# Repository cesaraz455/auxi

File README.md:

# auxi

**auxi** es un pequeño robot de fútbol para una competencia universitaria de robots, un proyecto de primer semestre. Este repositorio contiene el diseño en KiCad de su única PCB.

Toda la documentación del proyecto (decisiones de diseño, alimentación, pines, conectores, chasis, armado de la placa y puntos abiertos) está en un solo archivo: **[`CLAUDE.md`](CLAUDE.md)**.

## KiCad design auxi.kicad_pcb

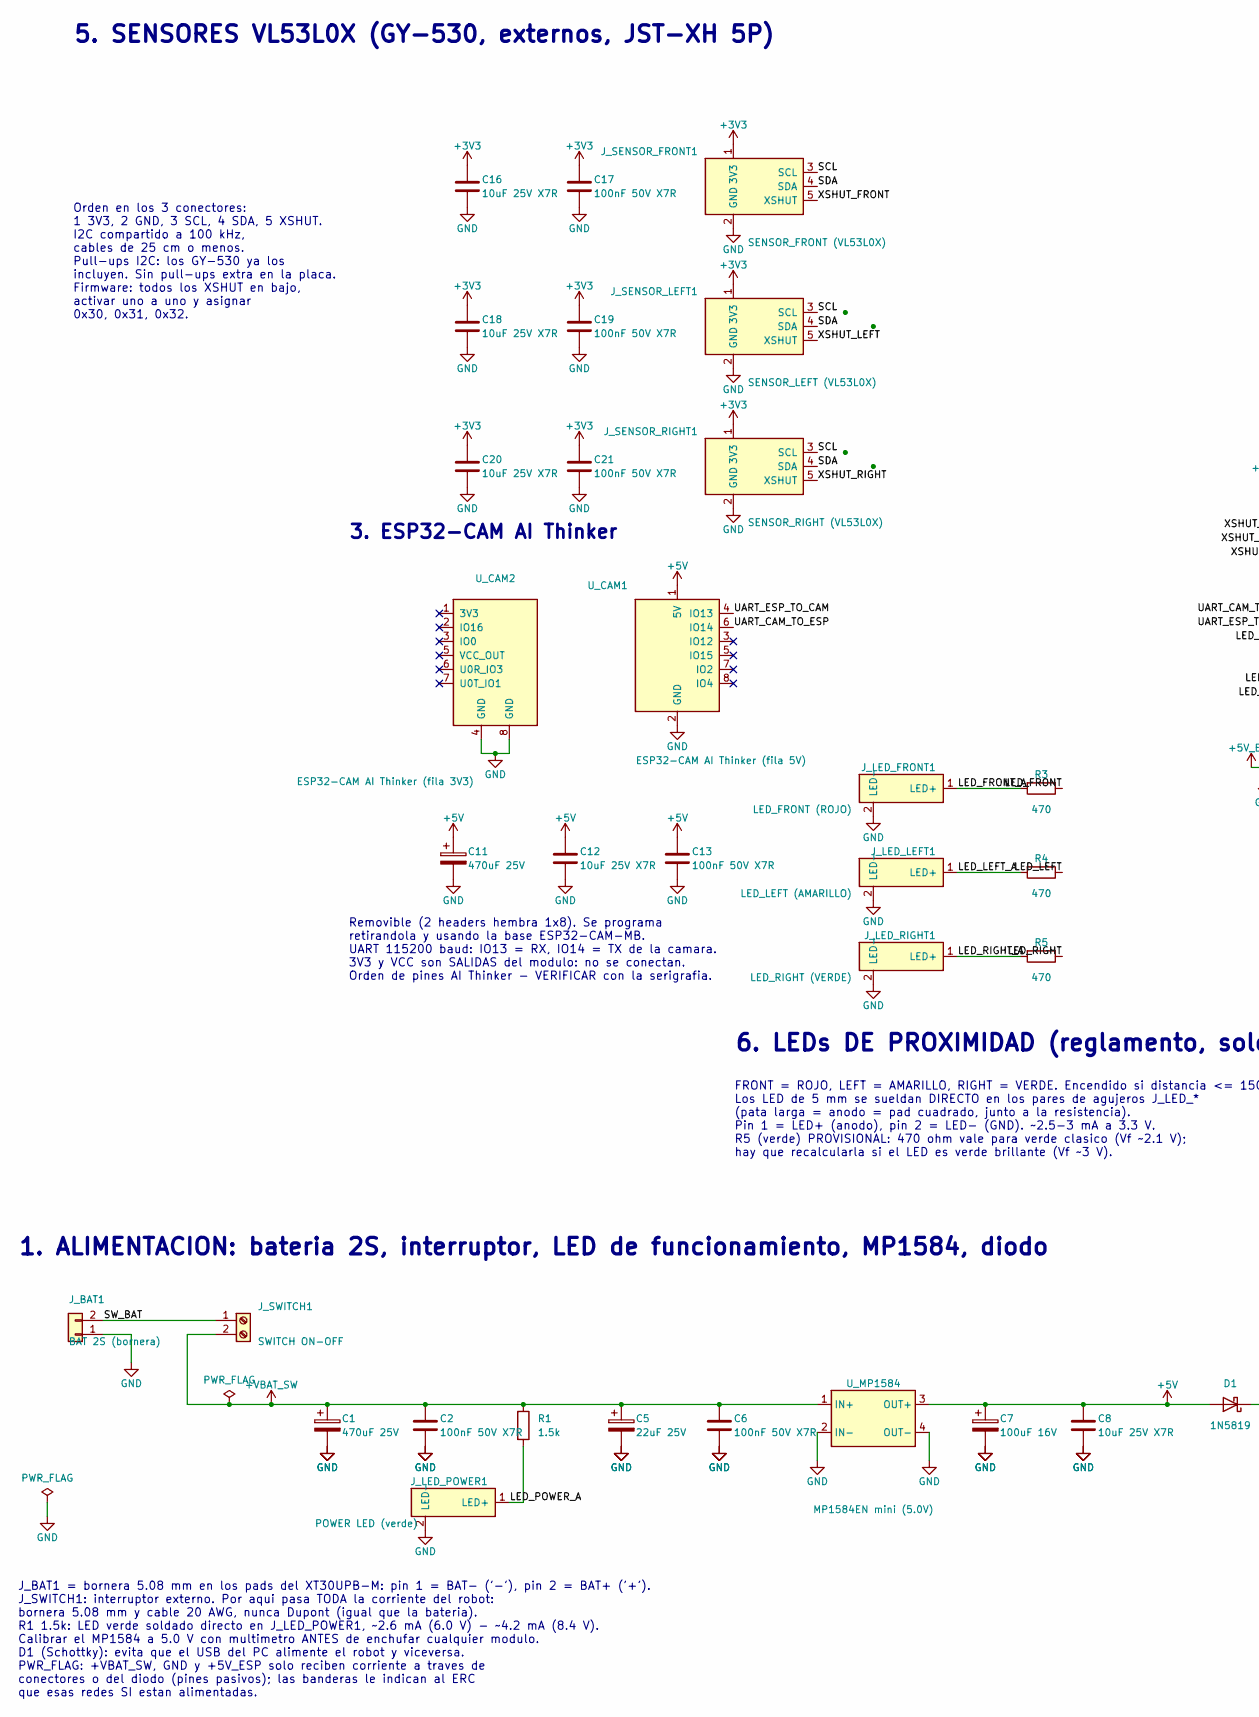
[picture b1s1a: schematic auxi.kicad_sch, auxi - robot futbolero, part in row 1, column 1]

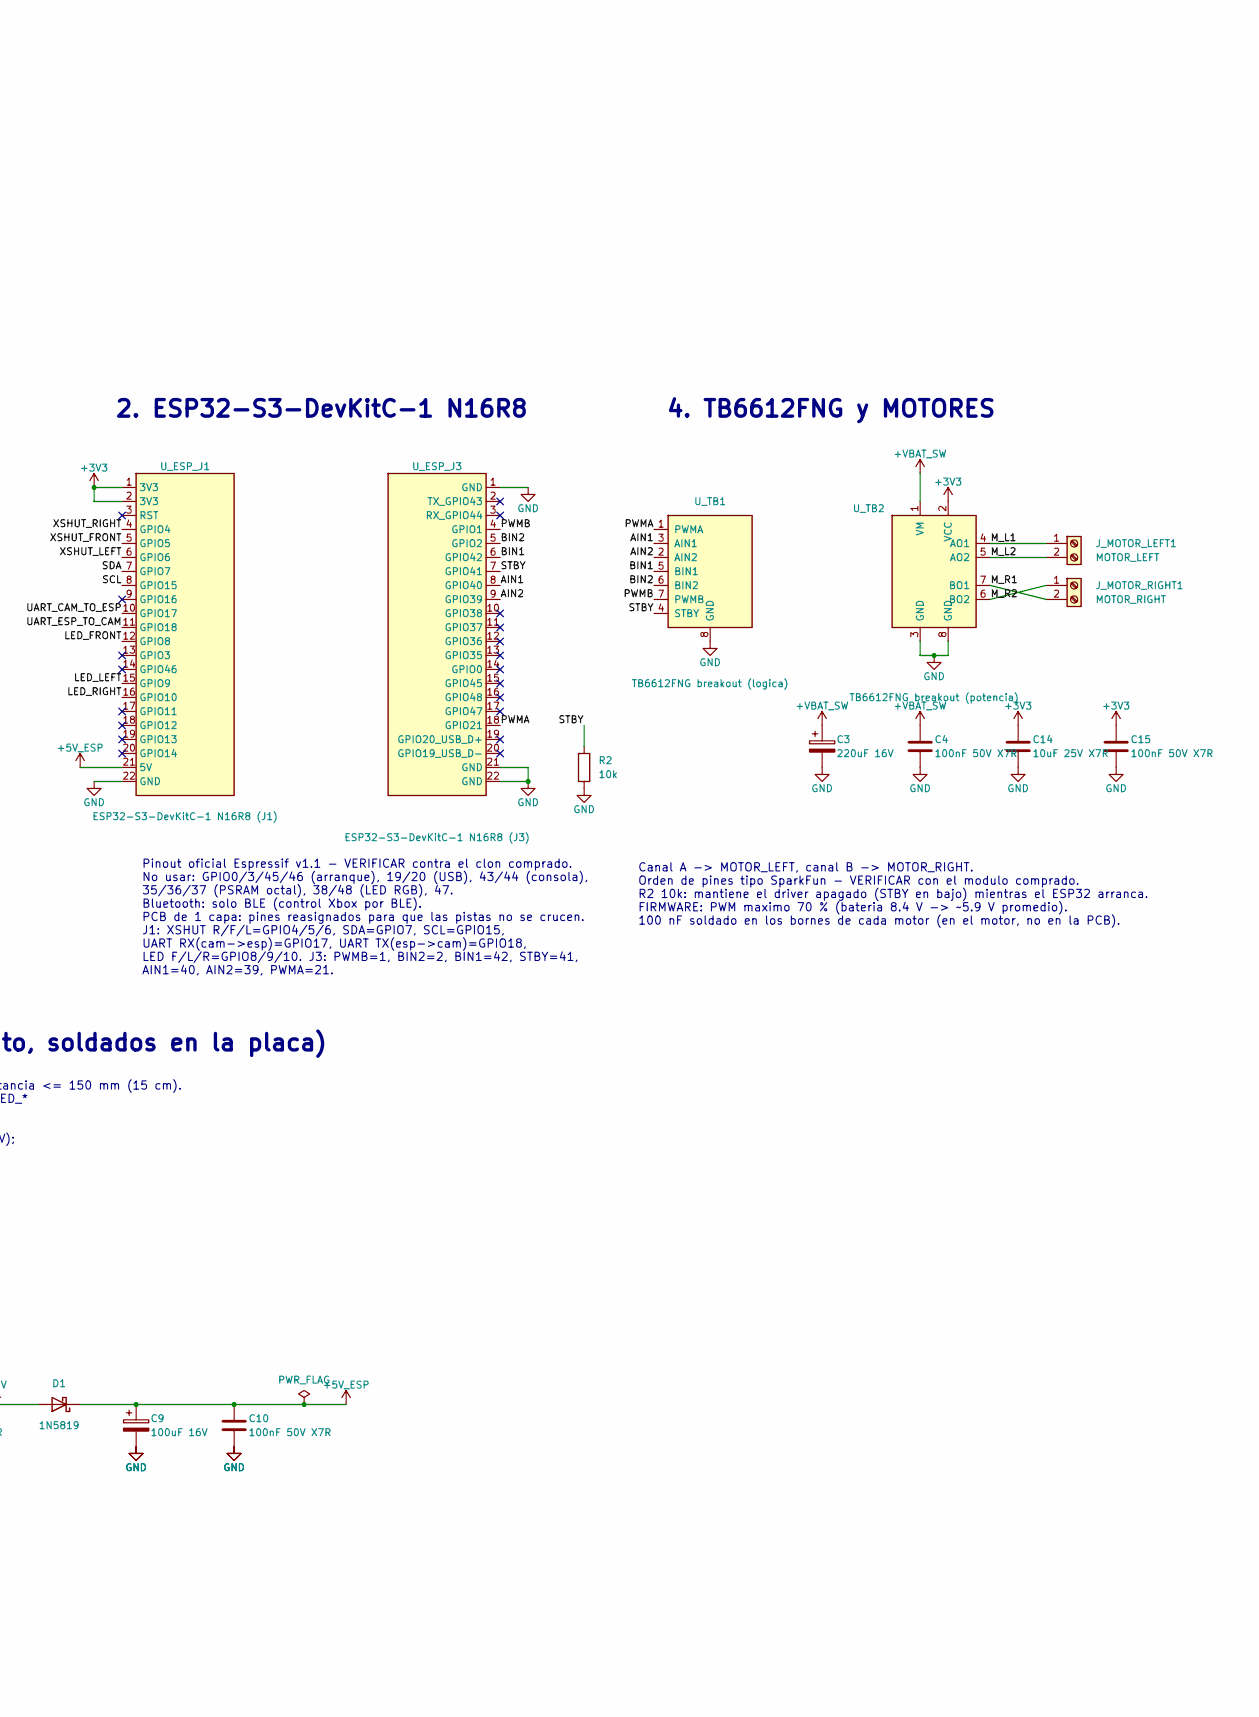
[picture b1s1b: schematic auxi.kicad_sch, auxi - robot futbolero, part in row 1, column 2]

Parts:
C1, C11: 470uF 25V; CP_Radial_D10.0mm_P5.00mm
C2, C4, C6, C10, C13, C15, C17, C19, C21: 100nF 50V X7R; C_Disc_D5.0mm_W2.5mm_P5.00mm
C3: 220uF 16V; CP_Radial_D8.0mm_P3.50mm
C5: 22uF 25V; CP_Radial_D5.0mm_P2.00mm
C7, C9: 100uF 16V; CP_Radial_D6.3mm_P2.50mm
C8, C12, C14, C16, C18, C20: 10uF 25V X7R; C_Rect_L7.0mm_W3.5mm_P5.00mm
D1: 1N5819; D_DO-41_SOD81_P10.16mm_Horizontal
J_BAT1: BAT 2S (bornera); AMASS_XT30UPB-M_1x02_P5.0mm_Vertical
J_LED_FRONT1: LED_FRONT (ROJO); PinHeader_1x02_P2.54mm_Vertical
J_LED_LEFT1: LED_LEFT (AMARILLO); PinHeader_1x02_P2.54mm_Vertical
J_LED_POWER1: POWER LED (verde); PinHeader_1x02_P2.54mm_Vertical
J_LED_RIGHT1: LED_RIGHT (VERDE); PinHeader_1x02_P2.54mm_Vertical
J_MOTOR_LEFT1: MOTOR_LEFT; TerminalBlock_Phoenix_MKDS-1,5-2-5.08_1x02_P5.08mm_Horizont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
J_MOTOR_RIGHT1: MOTOR_RIGHT; TerminalBlock_Phoenix_MKDS-1,5-2-5.08_1x02_P5.08mm_Horizont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
J_SENSOR_FRONT1: SENSOR_FRONT (VL53L0X); JST_XH_B5B-XH-A_1x05_P2.50mm_Vertical
J_SENSOR_LEFT1: SENSOR_LEFT (VL53L0X); JST_XH_B5B-XH-A_1x05_P2.50mm_Vertical
J_SENSOR_RIGHT1: SENSOR_RIGHT (VL53L0X); JST_XH_B5B-XH-A_1x05_P2.50mm_Vertical
J_SWITCH1: SWITCH ON-OFF; TerminalBlock_Phoenix_MKDS-1,5-2-5.08_1x02_P5.08mm_Horizont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
R1: 1.5k; R_Axial_DIN0207_L6.3mm_D2.5mm_P7.62mm_Horizontal
R2: 10k; R_Axial_DIN0207_L6.3mm_D2.5mm_P7.62mm_Horizontal
R3, R4, R5: 470; R_Axial_DIN0207_L6.3mm_D2.5mm_P7.62mm_Horizontal
U_CAM1: ESP32-CAM AI Thinker (fila 5V); PinSocket_1x08_P2.54mm_Vertical
U_CAM2: ESP32-CAM AI Thinker (fila 3V3); PinSocket_1x08_P2.54mm_Vertical
U_ESP_J1: ESP32-S3-DevKitC-1 N16R8 (J1); PinSocket_1x22_P2.54mm_Vertical
U_ESP_J3: ESP32-S3-DevKitC-1 N16R8 (J3); PinSocket_1x22_P2.54mm_Vertical
U_MP1584: MP1584EN mini (5.0V); MP1584_Mini_PROVISIONAL
U_TB1: TB6612FNG breakout (logica); PinSocket_1x08_P2.54mm_Vertical
U_TB2: TB6612FNG breakout (potencia); PinSocket_1x08_P2.54mm_Vertical

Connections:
+3V3: C14.1, C15.1, C16.1, C17.1, C18.1, C19.1, C20.1, C21.1, J_SENSOR_FRONT1.1 (3V3), J_SENSOR_LEFT1.1 (3V3), J_SENSOR_RIGHT1.1 (3V3), U_ESP_J1.1 (3V3), U_ESP_J1.2 (3V3), U_TB2.2 (VCC)
+5V: C7.1, C8.1, C11.1, C12.1, C13.1, D1.2 (A), U_CAM1.1 (5V), U_MP1584.3 (OUT+)
+5V_ESP: C9.1, C10.1, D1.1 (K), U_ESP_J1.21 (5V)
+VBAT_SW: C1.1, C2.1, C3.1, C4.1, C5.1, C6.1, J_SWITCH1.2, R1.1, U_MP1584.1 (IN+), U_TB2.1 (VM)
AIN1: U_ESP_J3.8 (GPIO40), U_TB1.3 (AIN1)
AIN2: U_ESP_J3.9 (GPIO39), U_TB1.2 (AIN2)
BIN1: U_ESP_J3.6 (GPIO42), U_TB1.5 (BIN1)
BIN2: U_ESP_J3.5 (GPIO2), U_TB1.6 (BIN2)
GND: C1.2, C2.2, C3.2, C4.2, C5.2, C6.2, C7.2, C8.2, C9.2, C10.2, C11.2, C12.2, C13.2, C14.2, C15.2, C16.2, C17.2, C18.2, C19.2, C20.2, C21.2, J_BAT1.1, J_LED_FRONT1.2 (LED-), J_LED_LEFT1.2 (LED-), J_LED_POWER1.2 (LED-), J_LED_RIGHT1.2 (LED-), J_SENSOR_FRONT1.2 (GND), J_SENSOR_LEFT1.2 (GND), J_SENSOR_RIGHT1.2 (GND), R2.2, U_CAM1.2 (GND), U_CAM2.4 (GND), U_CAM2.8 (GND), U_ESP_J1.22 (GND), U_ESP_J3.1 (GND), U_ESP_J3.21 (GND), U_ESP_J3.22 (GND), U_MP1584.2 (IN-), U_MP1584.4 (OUT-), U_TB1.8 (GND), U_TB2.3 (GND), U_TB2.8 (GND)
LED_FRONT: R3.1, U_ESP_J1.12 (GPIO8)
LED_FRONT_A: J_LED_FRONT1.1 (LED+), R3.2
LED_LEFT: R4.1, U_ESP_J1.15 (GPIO9)
LED_LEFT_A: J_LED_LEFT1.1 (LED+), R4.2
LED_POWER_A: J_LED_POWER1.1 (LED+), R1.2
LED_RIGHT: R5.1, U_ESP_J1.16 (GPIO10)
LED_RIGHT_A: J_LED_RIGHT1.1 (LED+), R5.2
M_L1: J_MOTOR_LEFT1.1, U_TB2.4 (AO1)
M_L2: J_MOTOR_LEFT1.2, U_TB2.5 (AO2)
M_R1: J_MOTOR_RIGHT1.2, U_TB2.7 (BO1)
M_R2: J_MOTOR_RIGHT1.1, U_TB2.6 (BO2)
PWMA: U_ESP_J3.18 (GPIO21), U_TB1.1 (PWMA)
PWMB: U_ESP_J3.4 (GPIO1), U_TB1.7 (PWMB)
SCL: J_SENSOR_FRONT1.3 (SCL), J_SENSOR_LEFT1.3 (SCL), J_SENSOR_RIGHT1.3 (SCL), U_ESP_J1.8 (GPIO15)
SDA: J_SENSOR_FRONT1.4 (SDA), J_SENSOR_LEFT1.4 (SDA), J_SENSOR_RIGHT1.4 (SDA), U_ESP_J1.7 (GPIO7)
STBY: R2.1, U_ESP_J3.7 (GPIO41), U_TB1.4 (STBY)
SW_BAT: J_BAT1.2, J_SWITCH1.1
UART_CAM_TO_ESP: U_CAM1.6 (IO14), U_ESP_J1.10 (GPIO17)
UART_ESP_TO_CAM: U_CAM1.4 (IO13), U_ESP_J1.11 (GPIO18)
XSHUT_FRONT: J_SENSOR_FRONT1.5 (XSHUT), U_ESP_J1.5 (GPIO5)
XSHUT_LEFT: J_SENSOR_LEFT1.5 (XSHUT), U_ESP_J1.6 (GPIO6)
XSHUT_RIGHT: J_SENSOR_RIGHT1.5 (XSHUT), U_ESP_J1.4 (GPIO4)

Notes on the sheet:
1. ALIMENTACION: bateria 2S, interruptor, LED de funcionamiento, MP1584, diodo
J_BAT1 = bornera 5.08 mm en los pads del XT30UPB-M: pin 1 = BAT- ('-'), pin 2 = BAT+ ('+'). J_SWITCH1: interruptor externo. Por aqui pasa TODA la corriente del robot: bornera 5.08 mm y cable 20 AWG, nunca Dupont (igual que la bateria). R1 1.5k: LED verde soldado directo en J_LED_POWER1, ~2.6 mA (6.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
2. ESP32-S3-DevKitC-1 N16R8
Pinout oficial Espressif v1.1 - VERIFICAR contra el clon comprado. No usar: GPIO0/3/45/46 (arranque), 19/20 (USB), 43/44 (consola), 35/36/37 (PSRAM octal), 38/48 (LED RGB), 47. Bluetooth: solo BLE (control Xbox por BLE). PCB de 1 capa: pines reasignados para que las pistas no se crucen. J1: XSHUT R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
3. ESP32-CAM AI Thinker
Removible (2 headers hembra 1x8). Se programa retirandola y usando la base ESP32-CAM-MB. UART 115200 baud: IO13 = RX, IO14 = TX de la camara. 3V3 y VCC son SALIDAS del modulo: no se conectan. Orden de pines AI Thinker - VERIFICAR con la serigrafia.
4. TB6612FNG y MOTORES
Canal A -> MOTOR_LEFT, canal B -> MOTOR_RIGHT. Orden de pines tipo SparkFun - VERIFICAR con el modulo comprado. R2 10k: mantiene el driver apagado (STBY en bajo) mientras el ESP32 arranca. FIRMWARE: PWM maximo 70 % (bateria 8.4 V -> ~5.9 V promedio). 100 nF soldado en los bornes de cada motor (en e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
5. SENSORES VL53L0X (GY-530, externos, JST-XH 5P)
Orden en los 3 conectores: 1 3V3, 2 GND, 3 SCL, 4 SDA, 5 XSHUT. I2C compartido a 100 kHz, cables de 25 cm o menos. Pull-ups I2C: los GY-530 ya los incluyen. Sin pull-ups extra en la placa. Firmware: todos los XSHUT en bajo, activar uno a uno y asignar 0x30, 0x31, 0x32.
6. LEDs DE PROXIMIDAD (reglamento, soldados en la placa)
FRONT = ROJO, LEFT = AMARILLO, RIGHT = VERDE. Encendido si distancia <= 150 mm (15 cm). Los LED de 5 mm se sueldan DIRECTO en los pares de agujeros J_LED_* (pata larga = anodo = pad cuadrado, junto a la resistencia). Pin 1 = LED+ (anodo), pin 2 = LED- (GND). ~2.5-3 mA a 3.3 V. R5 (verde) PROVISIONA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

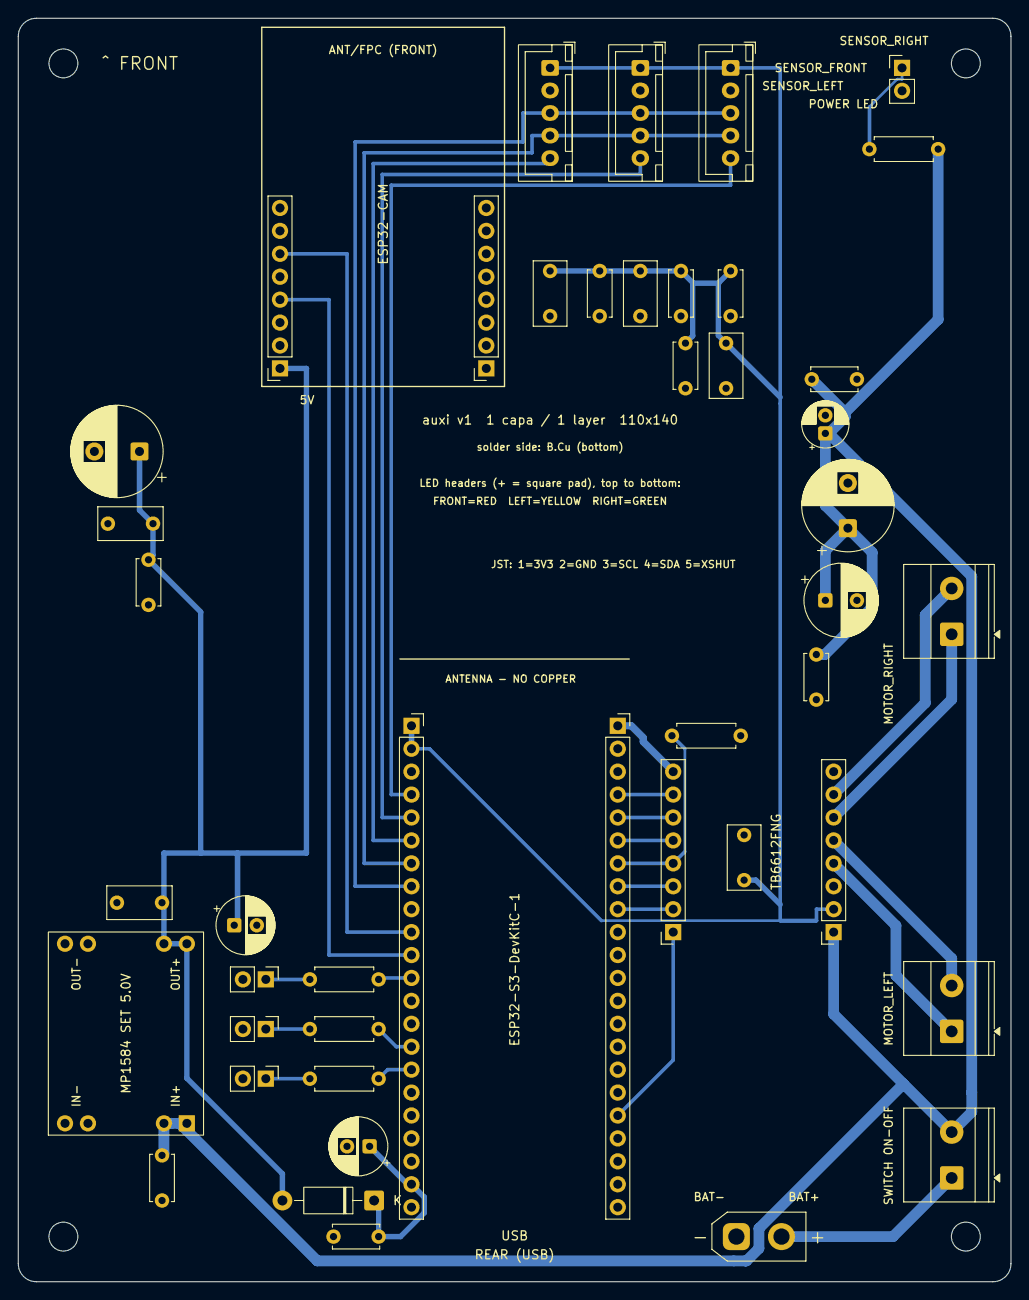
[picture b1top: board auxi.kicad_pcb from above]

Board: 2 copper layers, 110.0 x 140.0 mm, 49 parts (0 on the bottom side), 31 nets.

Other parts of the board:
H1, H2, H3, H4: MountingHole_3.2mm_M3
